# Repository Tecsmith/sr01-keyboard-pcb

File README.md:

# SR01-Keyboard-PCB

> **Note:** Rev "D" is a full redo in KiCAD, and has not been tested -- so, not suitable to build just yet.

## Intent

The 1-key<small><sup>1</sup></small> *"keyboard"* development platform.

## Features

This is not a "keyboard" per-se, it's a PCB that allows you you, with a **SeeedStudio** <a href="https://www.seeedstudio.com/XIAO-RP2040-v1-0-p-5026.html">XIAO RP2040</a> or <a href="https://www.seeedstudio.com/Seeed-XIAO-BLE-nRF52840-p-5201.html">XIAO nRF52840</a> module, to build:

* a 1-key MX-switch keyboard, with an RGB LED, <br>- *or* -
* a EC11 Rotary Encoder, with 4 RGB LED's, <br>- *or* -
* a 1-key HE *(Hall Effect)* switch keyboard, with a RGB LED, <br>- *or* -
* a 1-key EC *(Electrro Capacitance)* switch keyboard, <br> - *or* -
* a WHID solution, when *(the XIAO RP2040 is)* paired with a **SeeedStudio**:
  * <a href="https://www.seeedstudio.com/Seeed-Studio-XIAO-ESP32C6-p-5884.html">XIAO ESP32C6</a> module. [*Recommended*] , *- or -*
  * <a href="https://www.seeedstudio.com/Seeed-XIAO-ESP32C3-p-5431.html">XIAO ESP32C3</a> module, *- or -*
  * <a href="https://www.seeedstudio.com/XIAO-ESP32S3-p-5627.html">XIAO ESP32S3</a> module

for you to do some experimentations on.  These modules are intended to be breadboard mountable to that you can prototype your firmware and hardware ideas into verifiable solutions.

## Why?

When I built the SR61, one of the MicroMod modules I wanted to build for was the [SparkFun MicroMod ESP32 Processor](https://www.sparkfun.com/products/16781).. and for that I bought a [April Brother WHID Cactus](https://store.aprbrother.com/product/wifi-hid-injector) ... and then never got around to it.

The intent was to create a Wireless KB *(like a BT or 2.4GHz KB, but with WiFi)*, and also a whole bunch of additional features like a virtual web-KB, or the ability to configure the keys via it's own web interface.

This project is evolution of that idea.  *(The WHID Cactus is a ATmega 32u4 and ESP-12S combo. Old and limited.)*

And then the thought was: Why not also make it a Adafruit NeoKey Trinkey- / DigiSpark ATtiny85 USB key- ... -like one key?

Anyway ... what came out is a platform to build 1-key solutions for testing features, or just to have a quick volume control / sleep keep-alive / whatever you want to **play** with ... [*Software examples TBA*]

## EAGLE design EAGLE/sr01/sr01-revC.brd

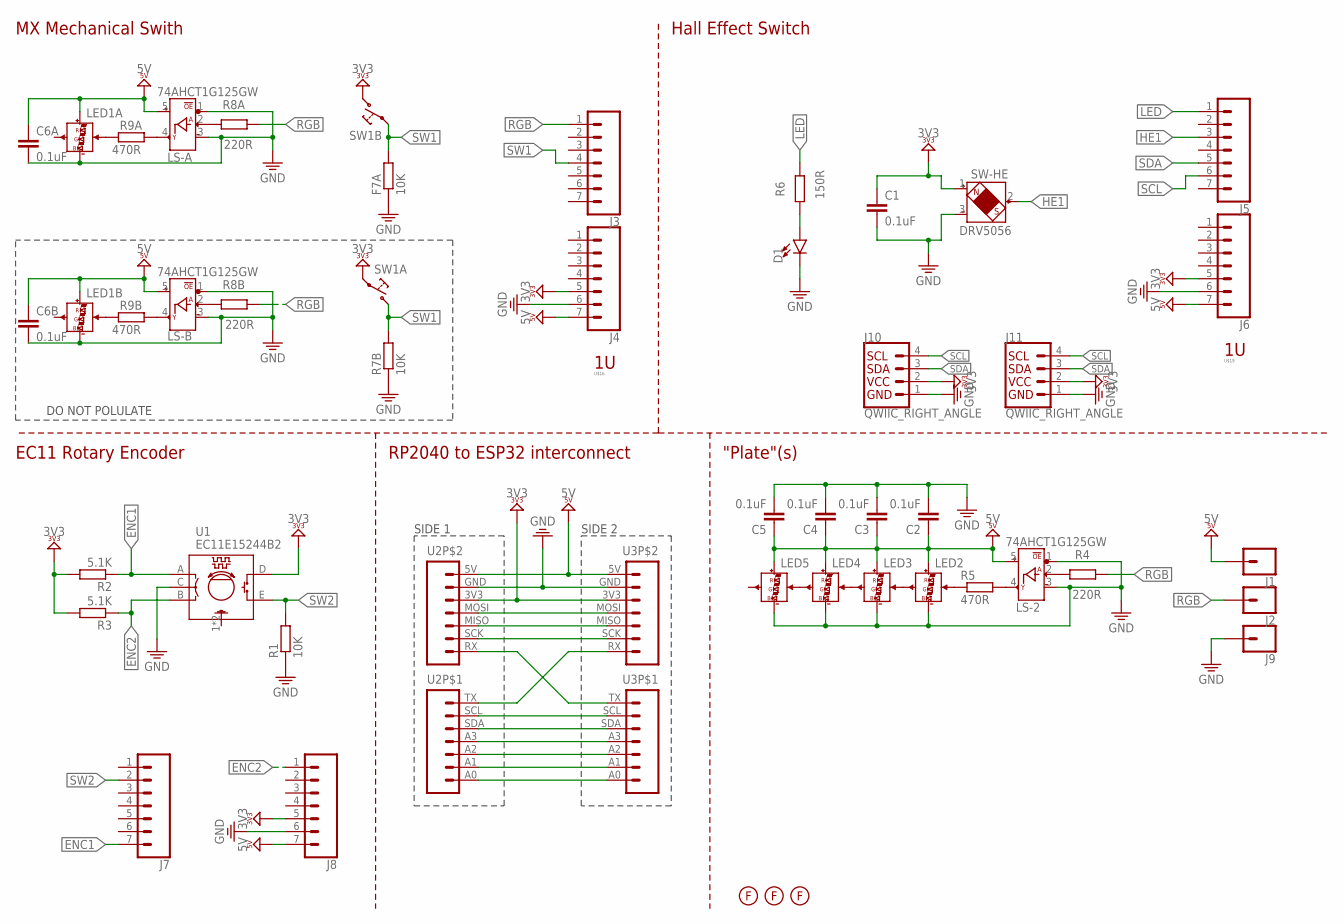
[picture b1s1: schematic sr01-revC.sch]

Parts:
C1, C2, C3, C4, C5, C6A, C6B: 0.1uF; C0603
D1: LED1206-BOTTOM; LED-1206-BOTTOM
F7A: 10K; R0603
J1, J2, J9: CONN_01PTH_NO_SILK_STAND; 1X01_NO_SILK_STAND
J3, J4, J5, J6, J7, J8: CONN_07; 1X07
J10, J11: QWIIC_RIGHT_ANGLE; JST04_1MM_RA
LED1A, LED1B, LED2, LED3, LED4, LED5: SK6812-MINI-ESK6812MINI-E; SK6812-E-MILL_V2
LS-2: 74AHCT1G125GW; SOT353
LS-A: 74AHCT1G125GW; SOT353
LS-B: 74AHCT1G125GW; SOT353
R1, R7B: 10K; R0603
R2, R3: 5.1K; R0603
R4, R8A, R8B: 220R; R0603
R5, R9A, R9B: 470R; R0603
R6: 150R; R0603
SW1A, SW1B: MX-5-PIN-HOTSWAP-VIANO-SILK; MX-5-PIN-HOTSWAP-VIA-NS
SW-HE: DRV5056; HE-2-PIN-HOTSWAP-NS
U1: EC11E15244B2; ROTARY_EC11E
U2, U3: MOUDLE-SEEEDUINO-XIAOSMD; MOUDLE14P-SMD-2.54-21X17.8MM
U$2, U$4, U$5: FIDUCIAL
U$16, U$19: MX-FPRINT-100U-DOC; MX-FPRINT-DOC-100U

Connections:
ENC1: J7.7, R2.1, U1.A
ENC2: J8.1, R3.1, U1.B
GND: C1.2, C2.2, C3.2, C4.2, C5.2, C6A.2, C6B.2, D1.C, F7A.1, J4.6, J6.6, J8.6, J9.1, J10.1, J11.1, LED1A.3-GND (GND), LED1B.3-GND (GND), LED2.3-GND (GND), LED3.3-GND (GND), LED4.3-GND (GND), LED5.3-GND (GND), LS-2.1 (!OE), LS-2.3 (3_GND), LS-A.1 (!OE), LS-A.3 (3_GND), LS-B.1 (!OE), LS-B.3 (3_GND), R1.1, R7B.1, SW-HE.3 (GND), U1.C, U2.GND (6), U3.GND (6)
HE1: J5.3, SW-HE.2 (OUT)
LED: J5.1, R6.2
unnamed: U2.RX (1), U3.TX (7)
unnamed: U2.SCL (6), U3.SCL (6)
unnamed: U2.SDA (5), U3.SDA (5)
unnamed: U2.A3 (4), U3.A3 (4)
unnamed: U2.A2 (3), U3.A2 (3)
unnamed: U2.A1 (2), U3.A1 (2)
unnamed: U2.A0 (1), U3.A0 (1)
unnamed: U2.TX (7), U3.RX (1)
unnamed: D1.A, R6.1
unnamed: LED1A.4-DIN (DIN), R9A.1
unnamed: LS-A.4 (Y_DOUT), R9A.2
unnamed: LED1B.4-DIN (DIN), R9B.1
unnamed: LS-B.4 (Y_DOUT), R9B.2
unnamed: LS-B.2 (A_DIN), R8B.1
unnamed: LS-A.2 (A_DIN), R8A.1
unnamed: U2.MOSI (4), U3.MOSI (4)
unnamed: U2.MISO (3), U3.MISO (3)
unnamed: U2.SCK (2), U3.SCK (2)
unnamed: LED2.4-DIN (DIN), R5.1
unnamed: LS-2.4 (Y_DOUT), R5.2
unnamed: LS-2.2 (A_DIN), R4.1
unnamed: LED2.2-DOUT (DOUT), LED3.4-DIN (DIN)
unnamed: LED3.2-DOUT (DOUT), LED4.4-DIN (DIN)
unnamed: LED4.2-DOUT (DOUT), LED5.4-DIN (DIN)
RGB: J2.1, J3.1, R4.2, R8A.2, R8B.2
SCL: J5.6, J10.4, J11.4
SDA: J5.5, J10.3, J11.3
SW1: F7A.2, J3.4, R7B.2, SW1A.1@1 (2), SW1A.1@2 (2), SW1B.2@1 (1), SW1B.2@2 (1)
SW2: J7.2, R1.2, U1.E
VCC3: C1.1, J4.5, J6.5, J8.5, J10.2, J11.2, R2.2, R3.2, SW1A.2@1 (1), SW1A.2@2 (1), SW1B.1@1 (2), SW1B.1@2 (2), SW-HE.1 (VDD), U1.D, U2.3V3 (5), U3.3V3 (5)
VCC5: C2.1, C3.1, C4.1, C5.1, C6A.1, C6B.1, J1.1, J4.7, J6.7, J8.7, LED1A.1-VDD (VDD), LED1B.1-VDD (VDD), LED2.1-VDD (VDD), LED3.1-VDD (VDD), LED4.1-VDD (VDD), LED5.1-VDD (VDD), LS-2.5 (5_VCC), LS-A.5 (5_VCC), LS-B.5 (5_VCC), U2.5V (7), U3.5V (7)

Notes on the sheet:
"Plate"(s)
MX Mechanical Swith
EC11 Rotary Encoder
Hall Effect Switch
RP2040 to ESP32 interconnect
DO NOT POLULATE
SIDE 1
SIDE 2

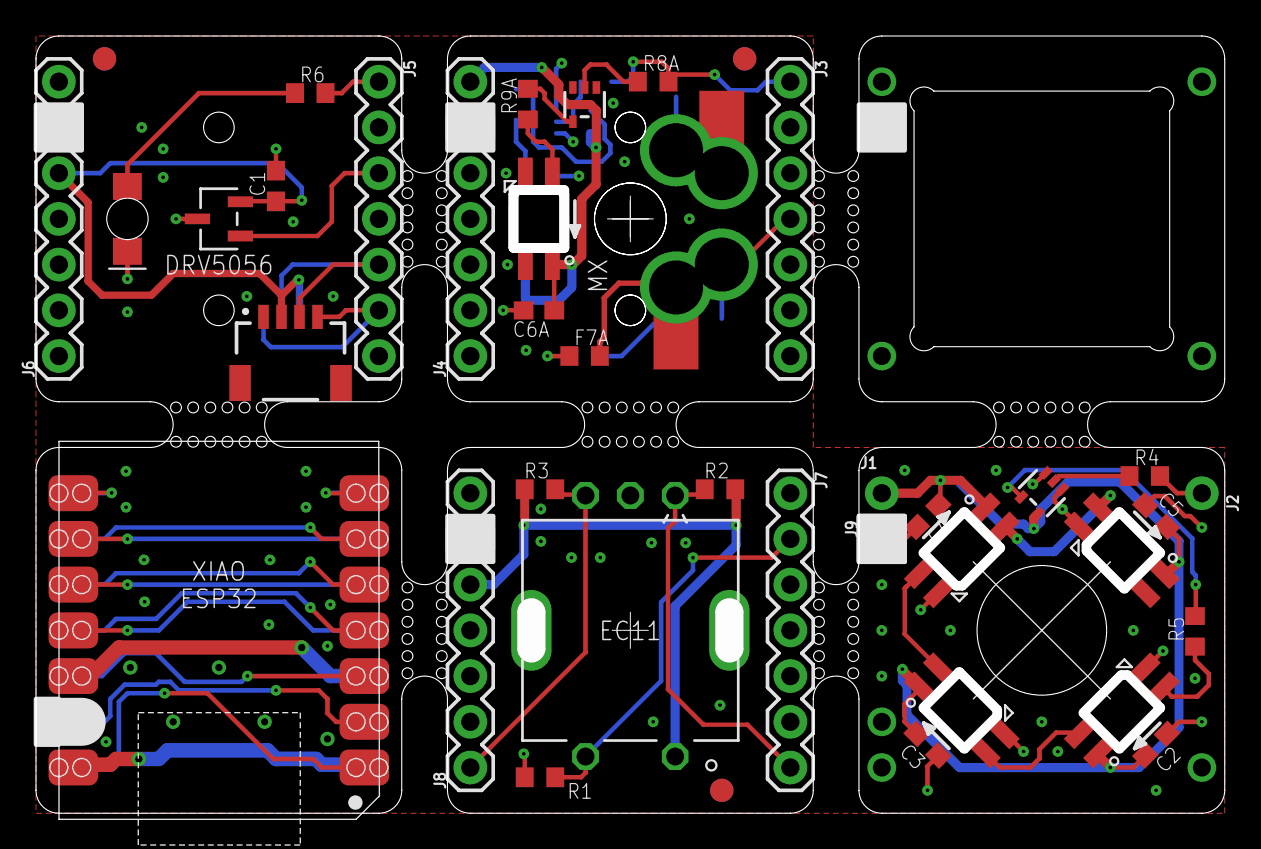
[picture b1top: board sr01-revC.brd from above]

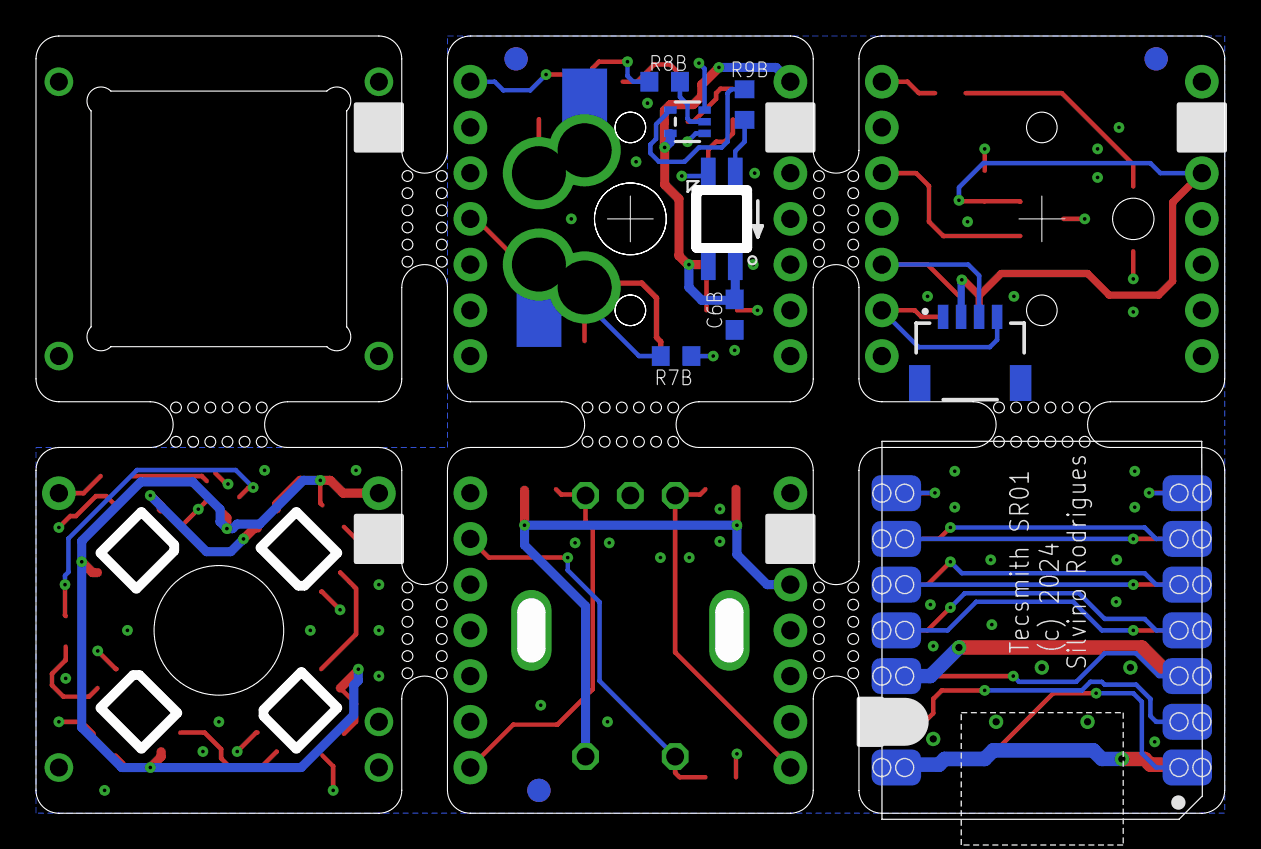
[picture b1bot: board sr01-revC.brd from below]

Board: 2 copper layers, 66.0 x 43.2 mm, 51 parts (14 on the bottom side), 36 nets.

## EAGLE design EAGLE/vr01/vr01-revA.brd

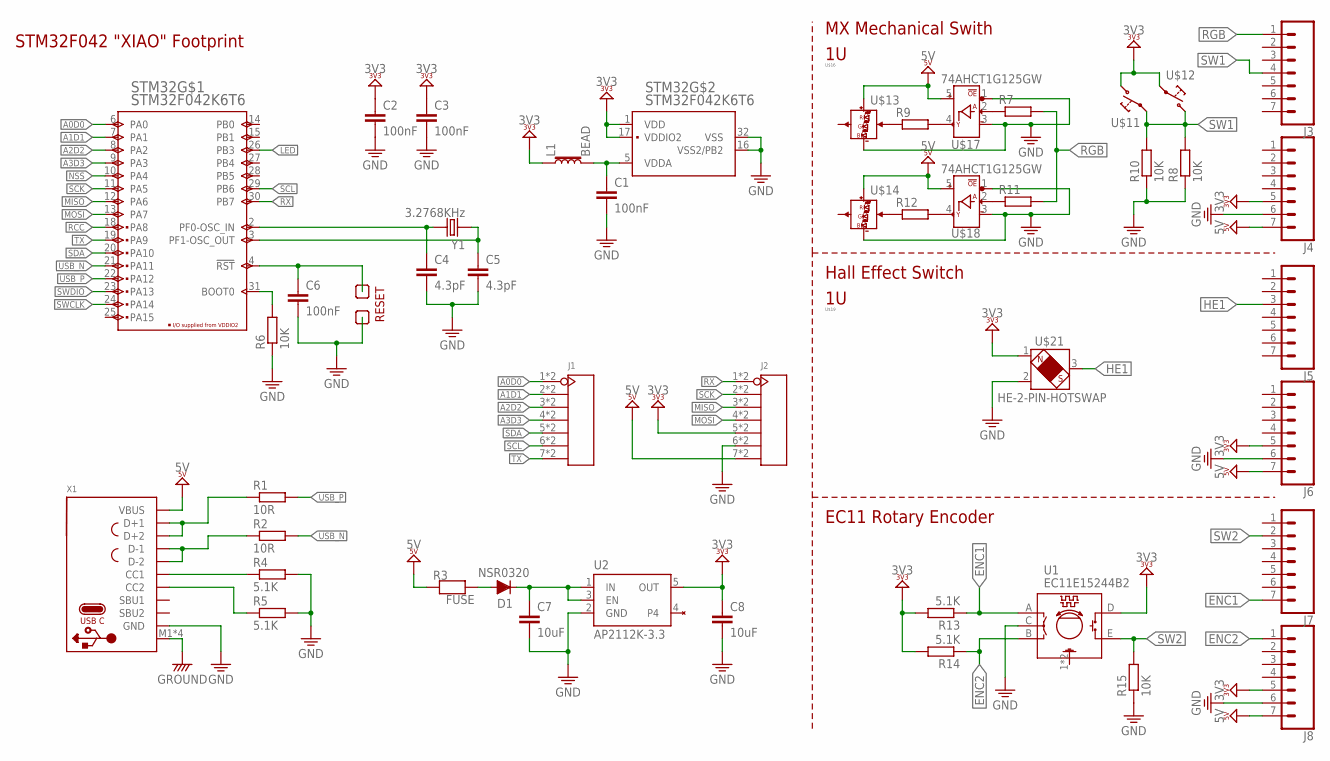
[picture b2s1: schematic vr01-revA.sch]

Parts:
C1, C2, C3, C6: 100nF; C0402K
C4, C5: 4.3pF; C0402K
C7, C8: 10uF; C0402K
D1: NSR0320; SOD-323F
J1, J2: HEADER-7P-HALF-HOLE-2.54; H7-HALF-HOLE-2.54
J3, J4, J5, J6, J7, J8: CONN_07; 1X07
L1: BEAD; 0402
R1, R2: 10R; R0402
R3: FUSE; 0805-NO
R4, R5: 5.1K; R0402
R6: 10K; R0402
R7, R9, R11, R12: R-EU_R0603; R0603
R8, R10, R15: 10K; R0603
R13, R14: 5.1K; R0603
STM32: STM32F042K6T6; LQFP-32
TP1, TP2: TEST-POINT.4RN; PAD.04X.04-RN
U1: EC11E15244B2; ROTARY_EC11E
U2: AP2112K-3.3; SOT23-5
U$11, U$12: MX-5-PIN-HOTSWAP-VIANO-SILK; MX-5-PIN-HOTSWAP-VIA-NS
U$13, U$14: SK6812-MINI-ESK6812MINI-E; SK6812-E-MILL_V2
U$16, U$19: MX-FPRINT-100U-DOC; MX-FPRINT-DOC-100U
U$17, U$18: 74AHCT1G125GW; SOT353
U$21: HE-2-PIN-HOTSWAP; HE-2-PIN-HOTSWAP-NS
X1: USB_C; TYPE-C-31-M-12
Y1: 3.2768KHz; X2-SMD-L2.0X1.2X0.55MM

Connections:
!RST: C6.1, STM32.4 (!RST), TP1.1
A0D0: J1.1, J1.13 (1), STM32.6 (PA0)
A1D1: J1.2, J1.14 (2), STM32.7 (PA1)
A2D2: J1.3, J1.15 (3), STM32.8 (PA2)
A3D3: J1.4, J1.16 (4), STM32.9 (PA3)
BOOT0: R6.2, STM32.31 (BOOT0)
ENC1: J7.7, R13.1, U1.A
ENC2: J8.1, R14.1, U1.B
GND: C1.2, C2.2, C3.2, C4.2, C5.2, C6.2, C7.2, C8.2, J2.6, J2.18 (6), J4.6, J6.6, J8.6, R4.2, R5.2, R6.1, R8.1, R10.1, R15.1, STM32.16 (VSS2/PB2), STM32.32 (VSS), TP2.1, U1.C, U2.2 (GND), U$13.3-GND (GND), U$14.3-GND (GND), U$17.1 (!OE), U$17.3 (3_GND), U$18.1 (!OE), U$18.3 (3_GND), U$21.2 (GND), X1.A1B12-GND (GND), X1.B1A12-GND (GND), X1.M1 (SHIELD), X1.M2 (SHIELD), X1.M3 (SHIELD), X1.M4 (SHIELD)
HE1: J5.3, U$21.3 (OUT)
LED: STM32.26 (PB3)
MISO: J2.3, J2.15 (3), STM32.12 (PA6)
MOSI: J2.4, J2.16 (4), STM32.13 (PA7)
unnamed: C1.1, L1.2, STM32.5 (VDDA)
unnamed: C4.1, STM32.2 (PF0-OSC_IN), Y1.2
unnamed: C5.1, STM32.3 (PF1-OSC_OUT), Y1.1
unnamed: R4.1, X1.A5-CC1 (CC1)
unnamed: R5.1, X1.B5-CC2 (CC2)
unnamed: C7.1, D1.C, U2.1 (IN), U2.3 (EN)
unnamed: D1.A, R3.2
unnamed: R1.1, X1.A6-DP1 (D+1), X1.B6-DP2 (D+2)
unnamed: R2.1, X1.A7-DN1 (D-1), X1.B7-DN2 (D-2)
unnamed: R9.1, U$13.4-DIN (DIN)
unnamed: R9.2, U$17.4 (Y_DOUT)
unnamed: R12.1, U$14.4-DIN (DIN)
unnamed: R12.2, U$18.4 (Y_DOUT)
unnamed: R11.1, U$18.2 (A_DIN)
unnamed: R7.1, U$17.2 (A_DIN)
NSS: STM32.10 (PA4)
RCC: STM32.18 (PA8)
RGB: J3.1, R7.2, R11.2
RX: J2.1, J2.13 (1), STM32.30 (PB7)
SCK: J2.2, J2.14 (2), STM32.11 (PA5)
SCL: J1.6, J1.18 (6), STM32.29 (PB6)
SDA: J1.5, J1.17 (5), STM32.20 (PA10)
SW1: J3.4, R8.2, R10.2, U$11.2@1 (1), U$11.2@2 (1), U$12.1@1 (2), U$12.1@2 (2)
SW2: J7.2, R15.2, U1.E
SWCLK: STM32.24 (PA14)
SWDIO: STM32.23 (PA13)
TX: J1.7, J1.19 (7), STM32.19 (PA9)
USB_N: R2.2, STM32.21 (PA11)
USB_P: R1.2, STM32.22 (PA12)
VCC3: C2.1, C3.1, C8.1, J2.5, J2.17 (5), J4.5, J6.5, J8.5, L1.1, R13.2, R14.2, STM32.1 (VDD), STM32.17 (VDDIO2), U1.D, U2.5 (OUT), U$11.1@1 (2), U$11.1@2 (2), U$12.2@1 (1), U$12.2@2 (1), U$21.1 (VDD)
VCC5: J2.7, J2.19 (7), J4.7, J6.7, J8.7, R3.1, U$13.1-VDD (VDD), U$14.1-VDD (VDD), U$17.5 (5_VCC), U$18.5 (5_VCC), X1.A4B9-VBUS (VBUS), X1.B4A9-VBUS (VBUS)

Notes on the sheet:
STM32F042 "XIAO" Footprint
MX Mechanical Swith
EC11 Rotary Encoder
RESET
Hall Effect Switch

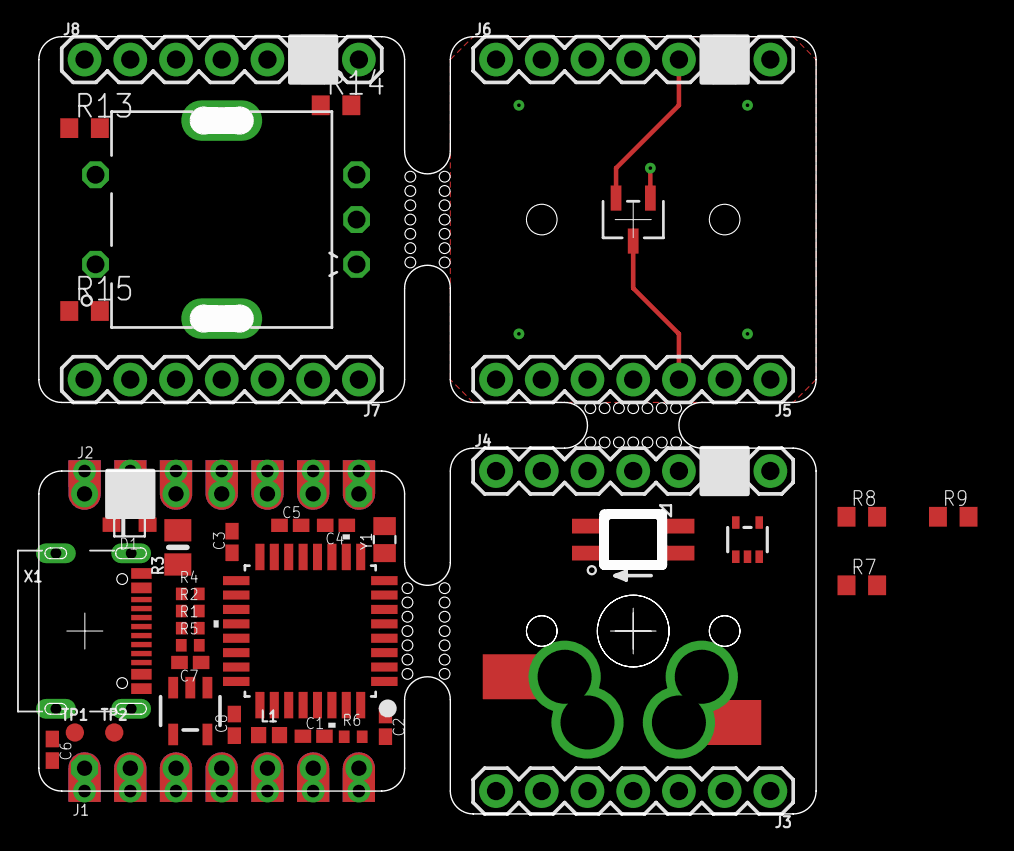
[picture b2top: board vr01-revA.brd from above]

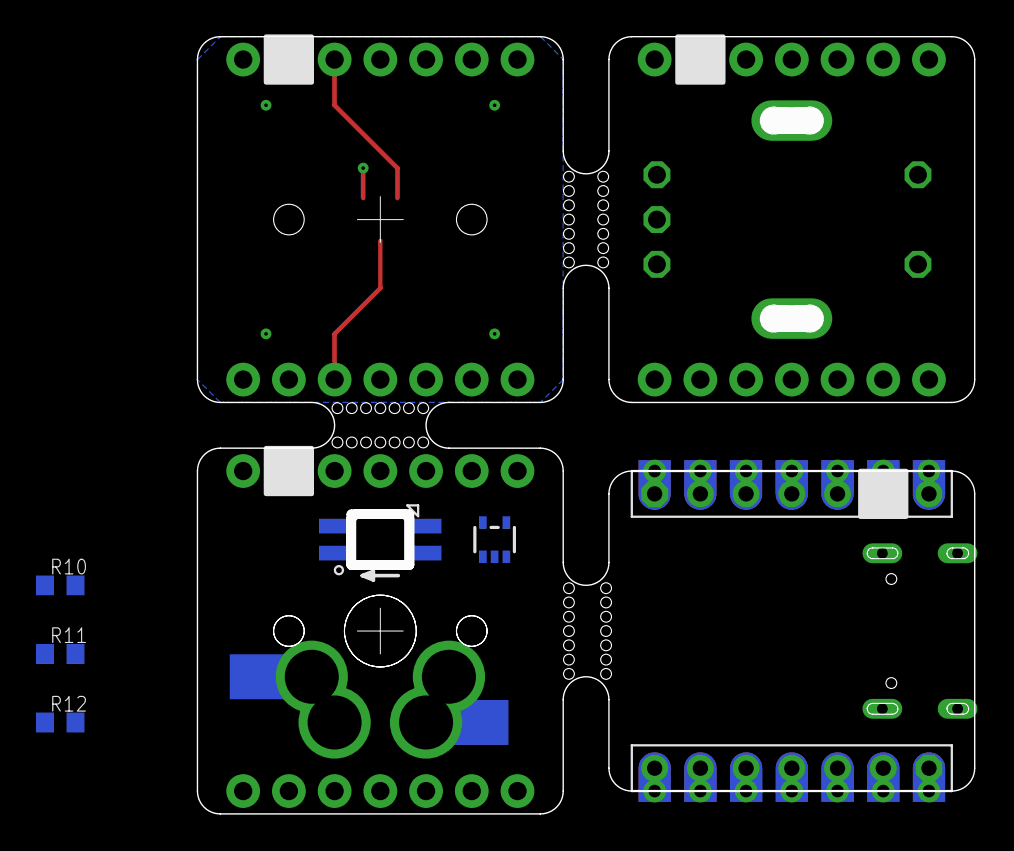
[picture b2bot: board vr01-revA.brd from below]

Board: 4 copper layers, 43.2 x 43.2 mm, 49 parts (7 on the bottom side), 39 nets.

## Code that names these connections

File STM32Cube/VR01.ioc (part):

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Mcu.Name=STM32F042K(4-6)Tx
Mcu.Package=LQFP32
Mcu.UserName=STM32F042K6Tx
PA0.Mode=IN0
PA0.Signal=ADC_IN0
PA1.Mode=IN1
PA1.Signal=ADC_IN1
PA10.Mode=I2C
PA10.Signal=I2C1_SDA
PA11.Mode=Device
PA11.Signal=USB_DM
PA12.Mode=Device
PA12.Signal=USB_DP
PA13.Mode=Serial_Wire
PA13.Signal=SYS_SWDIO
PA14.Mode=Serial_Wire
PA14.Signal=SYS_SWCLK
PA2.Mode=IN2
PA2.Signal=ADC_IN2
PA3.Mode=IN3
PA3.Signal=ADC_IN3
PA4.Mode=NSS_Signal_Hard_Input
PA4.Signal=SPI1_NSS
PA5.Mode=Full_Duplex_Slave
PA5.Signal=SPI1_SCK
PA6.Mode=Full_Duplex_Slave
PA6.Signal=SPI1_MISO
PA7.Mode=Full_Duplex_Slave
PA7.Signal=SPI1_MOSI
PA8.Mode=Clock-out
PA8.Signal=RCC_MCO
PA9.Mode=Asynchronous
PA9.Signal=USART1_TX
PB3.GPIOParameters=GPIO_Label
PB3.GPIO_Label=LED
PB3.Signal=GPIO_Output
PB6.Mode=I2C
PB6.Signal=I2C1_SCL
PB7.Mode=Asynchronous
PB7.Signal=USART1_RX
PF0-OSC_IN.Mode=HSE-External-Oscillator
PF0-OSC_IN.Signal=RCC_OSC_IN
PF1-OSC_OUT.Mode=HSE-External-Oscillator
PF1-OSC_OUT.Signal=RCC_OSC_OUT
RCC.SYSCLKFreq_VALUE=48000000
RCC.SYSCLKSource=RCC_SYSCLKSOURCE_HSI48
board=custom

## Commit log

2024-12-07 Rev C PCB
2026-04-29 Added KiCAD redo -- rev D
2026-05-02 add EC switch

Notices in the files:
EAGLE/sr01/sr01-revC.brd:
(c) 2024
parts and their libraries:
SparkFun-Connectors: Licensing: Creative Commons ShareAlike 4.0 International - https://creativecommons.org/licenses/by-sa/4.0
microbuilder: This work is placed in the public domain, and may be freely used for commercial and non-commercial work with the following conditions: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
